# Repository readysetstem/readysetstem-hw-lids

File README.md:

readysetstem-hw-lids
===========================

Ready Set STEM(TM) Lids hardware schematics and related documents

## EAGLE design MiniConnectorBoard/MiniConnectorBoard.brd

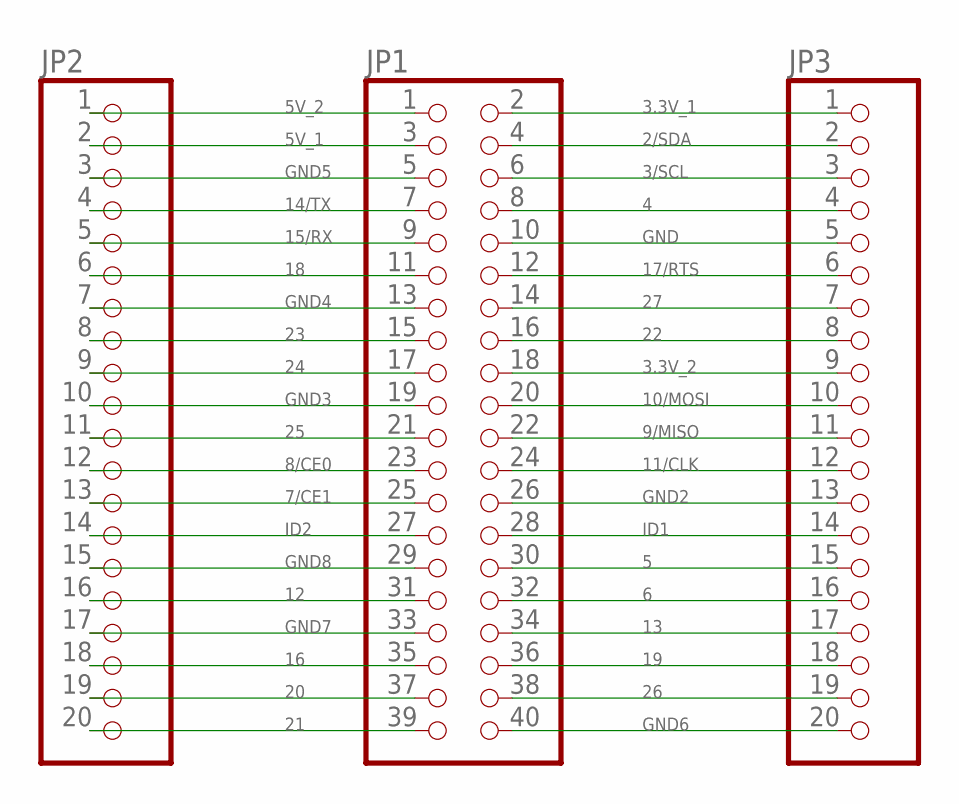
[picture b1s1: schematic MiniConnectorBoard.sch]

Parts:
JP1: NONE; 2X20
JP2, JP3: NONE; 1X20

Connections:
2/SDA: JP1.4, JP3.2
3.3V_1: JP1.2, JP3.1
3.3V_2: JP1.18, JP3.9
3/SCL: JP1.6, JP3.3
4: JP1.8, JP3.4
5: JP1.30, JP3.15
5V_1: JP1.3, JP2.2
5V_2: JP1.1, JP2.1
6: JP1.32, JP3.16
7/CE1: JP1.25, JP2.13
8/CE0: JP1.23, JP2.12
9/MISO: JP1.22, JP3.11
10/MOSI: JP1.20, JP3.10
11/CLK: JP1.24, JP3.12
12: JP1.31, JP2.16
13: JP1.34, JP3.17
14/TX: JP1.7, JP2.4
15/RX: JP1.9, JP2.5
16: JP1.35, JP2.18
17/RTS: JP1.12, JP3.6
18: JP1.11, JP2.6
19: JP1.36, JP3.18
20: JP1.37, JP2.19
21: JP1.39, JP2.20
22: JP1.16, JP3.8
23: JP1.15, JP2.8
24: JP1.17, JP2.9
25: JP1.21, JP2.11
26: JP1.38, JP3.19
27: JP1.14, JP3.7
GND: JP1.10, JP3.5
GND2: JP1.26, JP3.13
GND3: JP1.19, JP2.10
GND4: JP1.13, JP2.7
GND5: JP1.5, JP2.3
GND6: JP1.40, JP3.20
GND7: JP1.33, JP2.17
GND8: JP1.29, JP2.15
ID1: JP1.28, JP3.14
ID2: JP1.27, JP2.14

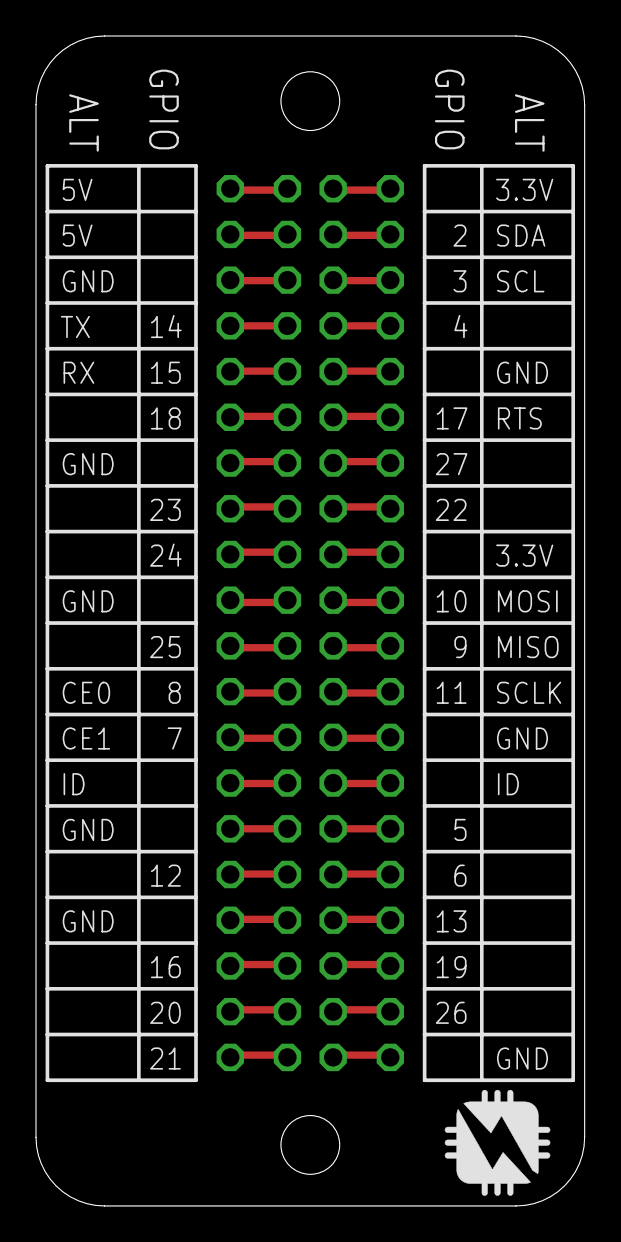
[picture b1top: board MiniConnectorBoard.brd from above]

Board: 2 copper layers, 30.5 x 65.0 mm, 3 parts (0 on the bottom side), 40 nets.

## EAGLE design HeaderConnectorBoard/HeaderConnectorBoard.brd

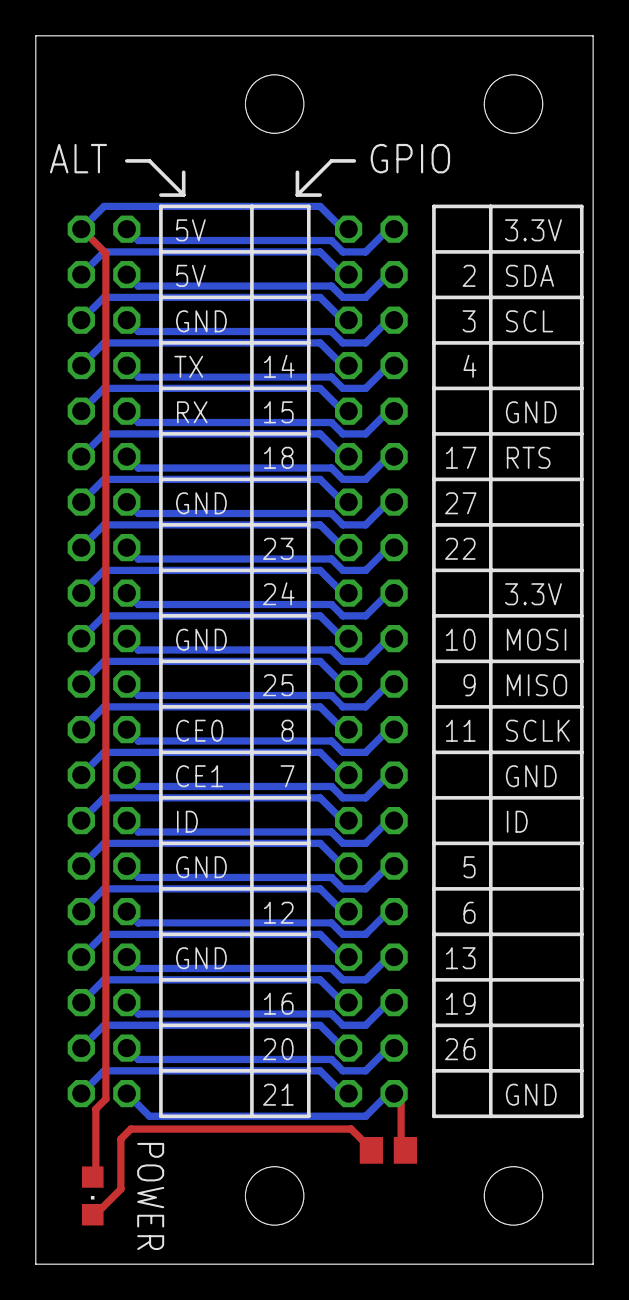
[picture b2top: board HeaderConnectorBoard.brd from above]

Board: 2 copper layers, 31.1 x 68.6 mm, 4 parts (0 on the bottom side), 41 nets.

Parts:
JP1, JP2: NONE; 2X20
LED1: 475-1410-2-ND; CHIPLED_0805
R1: 200; R0805

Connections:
2/SDA: JP1.4, JP2.4
3.3V_1: JP1.2, JP2.2
3.3V_2: JP1.18, JP2.18
3/SCL: JP1.6, JP2.6
4: JP1.8, JP2.8
5: JP1.30, JP2.30
5V_1: JP1.3, JP2.3
5V_2: JP1.1, JP2.1, LED1.A
6: JP1.32, JP2.32
7/CE1: JP1.25, JP2.25
8/CE0: JP1.23, JP2.23
9/MISO: JP1.22, JP2.22
10/MOSI: JP1.20, JP2.20
11/CLK: JP1.24, JP2.24
12: JP1.31, JP2.31
13: JP1.34, JP2.34
14/TX: JP1.7, JP2.7
15/RX: JP1.9, JP2.9
16: JP1.35, JP2.35
17/RTS: JP1.12, JP2.12
18: JP1.11, JP2.11
19: JP1.36, JP2.36
20: JP1.37, JP2.37
21: JP1.39, JP2.39
22: JP1.16, JP2.16
23: JP1.15, JP2.15
24: JP1.17, JP2.17
25: JP1.21, JP2.21
26: JP1.38, JP2.38
27: JP1.14, JP2.14
GND: JP1.10, JP2.10
GND2: JP1.26, JP2.26
GND3: JP1.19, JP2.19
GND4: JP1.13, JP2.13
GND5: JP1.5, JP2.5
GND6: JP1.40, JP2.40, R1.1
GND7: JP1.33, JP2.33
GND8: JP1.29, JP2.29
ID1: JP1.28, JP2.28
ID2: JP1.27, JP2.27
unnamed: LED1.C, R1.2

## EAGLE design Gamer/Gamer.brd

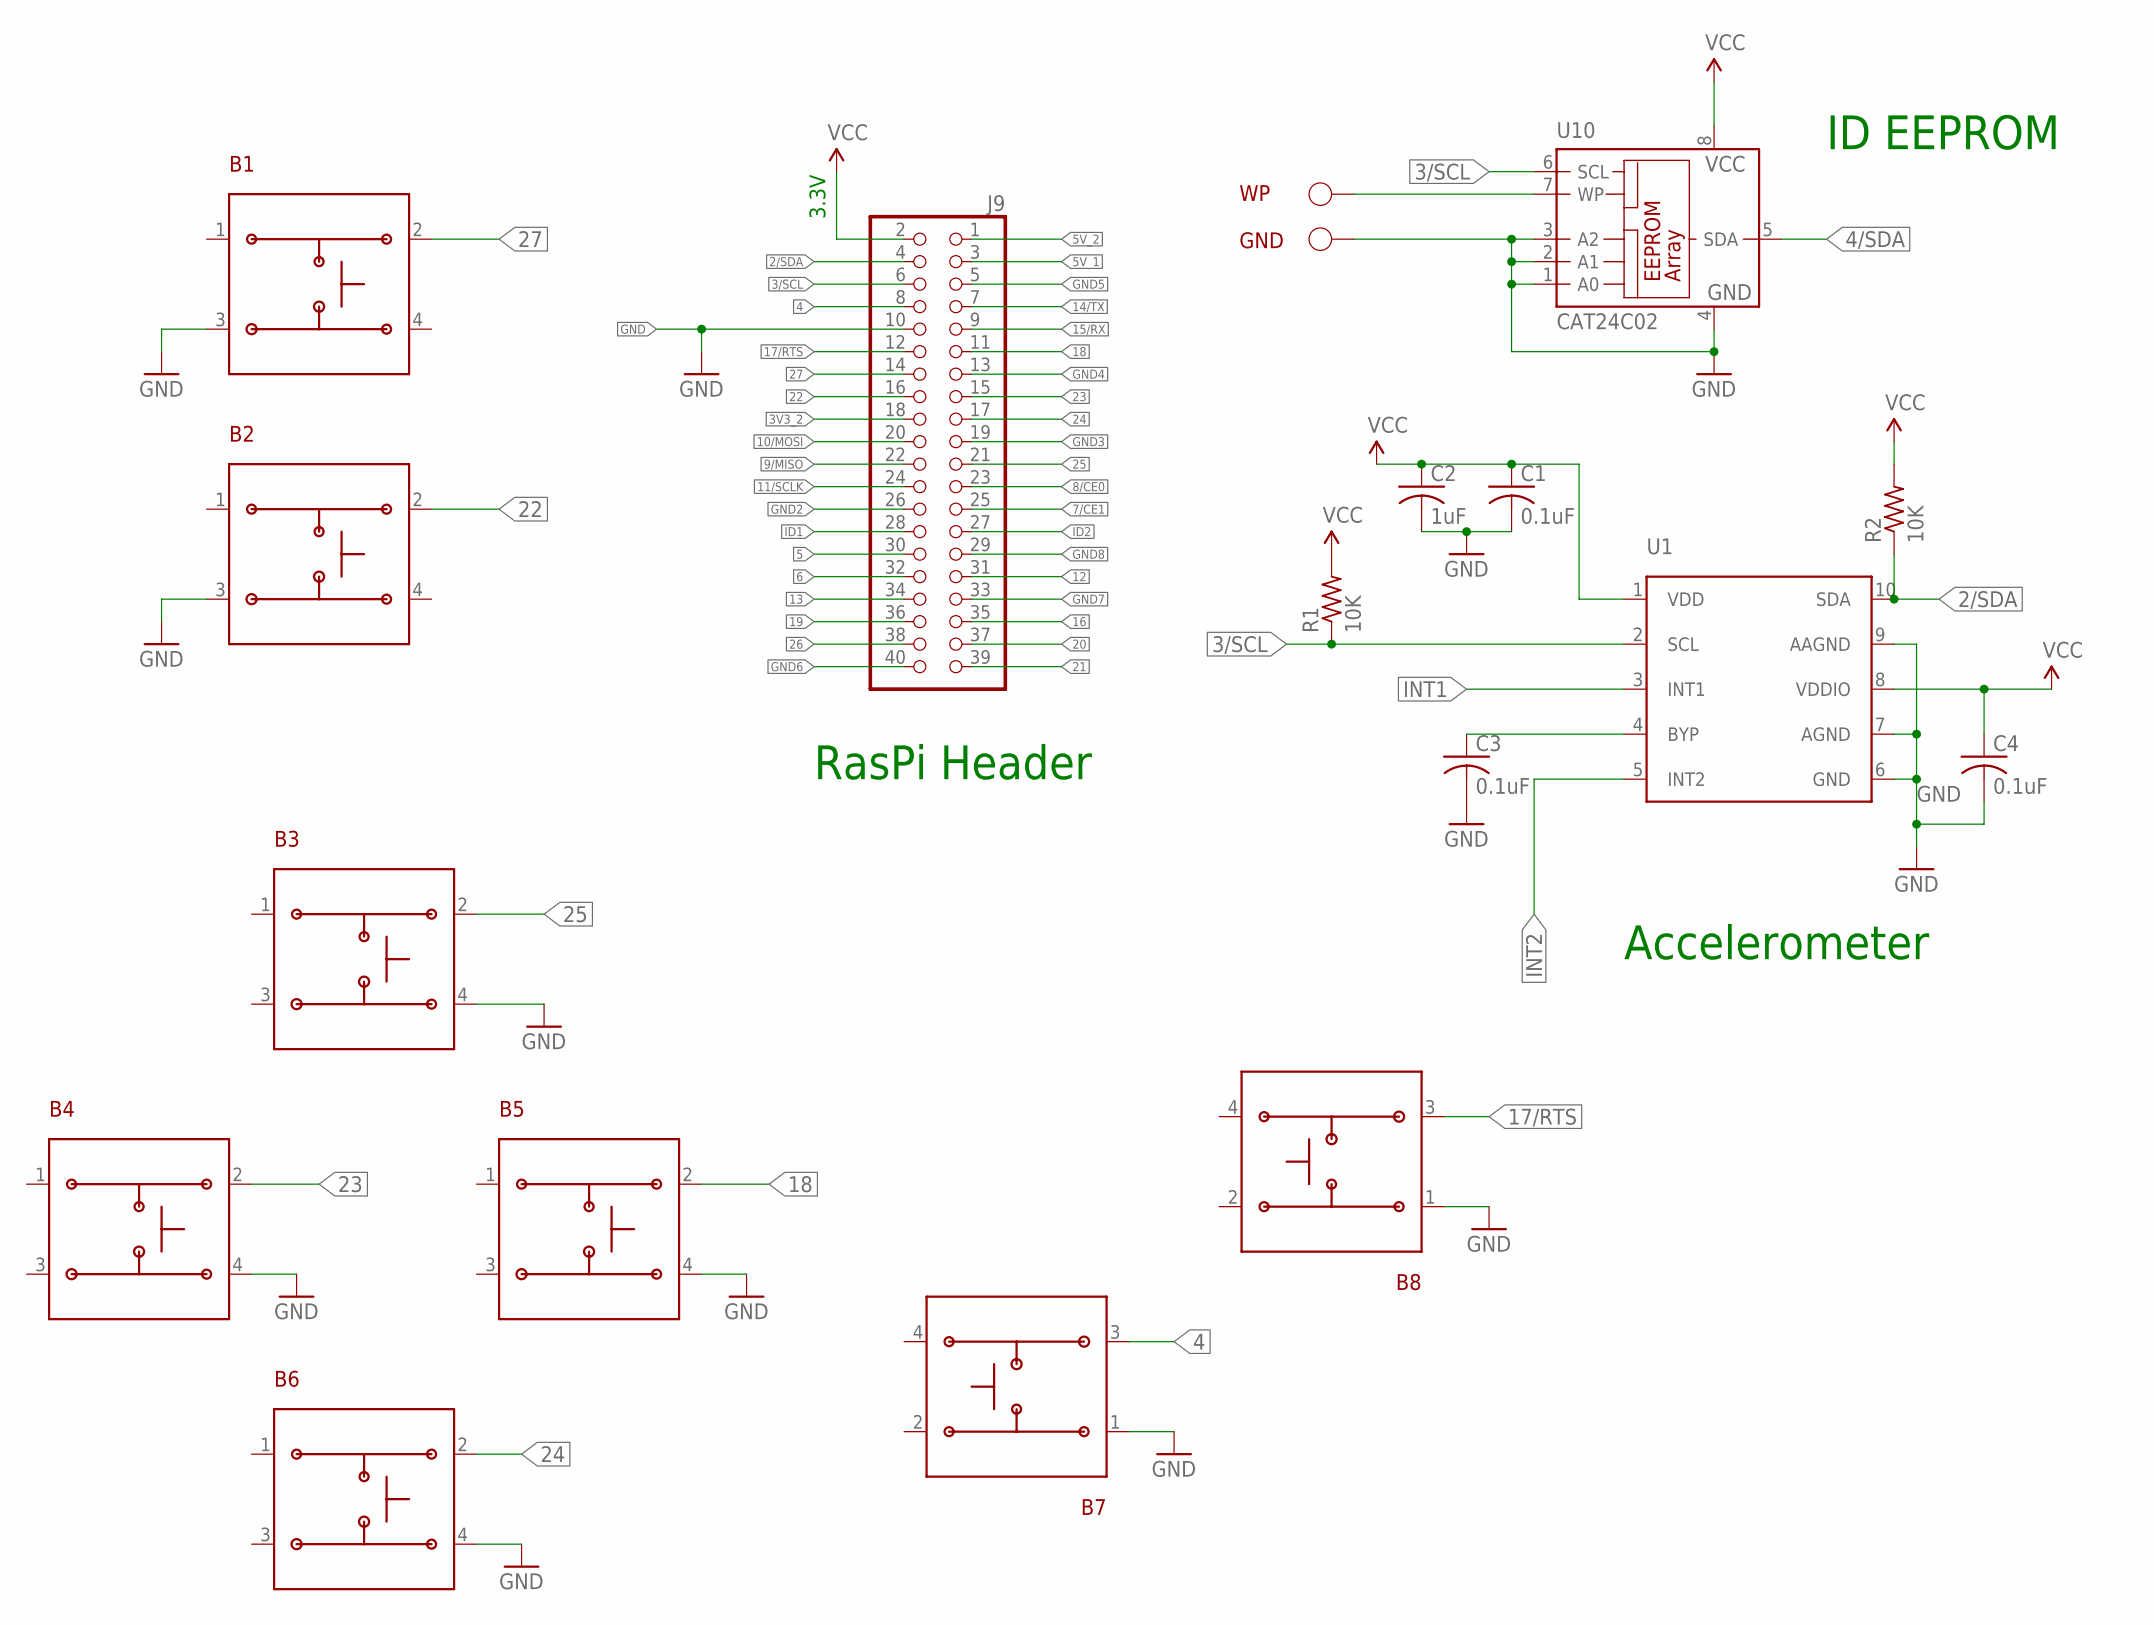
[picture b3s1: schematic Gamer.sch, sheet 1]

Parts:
B1, B2: 6X6MM_BUTTON
B3, B4, B5, B6, B7, B8: 12X12MM_BUTTON
C1, C3, C4: 0.1uF; C0603
C2: 1uF; C0603
GND: TESTPAD
J9: PINHD-2X20; 2X20
R1, R2: 10K; R0603
U1: MMA8653FCR1
U10: CAT24C02; TSSOP8
WP: TESTPAD

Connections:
2/SDA: J9.4, R2.1, U1.10 (SDA)
3/SCL: J9.6, R1.1, U1.2 (SCL), U10.6 (SCL)
3V3_2: J9.18
4: B7.3, J9.8
4/SDA: U10.5 (SDA)
5: J9.30
5V_1: J9.3
5V_2: J9.1
6: J9.32
7/CE1: J9.25
8/CE0: J9.23; also elsewhere on the board
9/MISO: J9.22; also elsewhere on the board
10/MOSI: J9.20; also elsewhere on the board
11/SCLK: J9.24; also elsewhere on the board
12: J9.31
13: J9.34
14/TX: J9.7
15/RX: J9.9
16: J9.35
17/RTS: B8.3, J9.12
18: B5.2, J9.11
19: J9.36
20: J9.37
21: J9.39
22: B2.2, J9.16
23: B4.2, J9.15
24: B6.2, J9.17
25: B3.2, J9.21
26: J9.38
27: B1.2, J9.14
GND: B1.3, B2.3, B3.4, B4.4, B5.4, B6.4, B7.1, B8.1, C1.2, C2.2, C3.2, C4.2, GND.1, J9.10, U1.6 (GND), U1.7 (AGND), U1.9 (AAGND), U10.1 (A0), U10.2 (A1), U10.3 (A2), U10.4 (GND); also elsewhere on the board
GND2: J9.26
GND3: J9.19
GND4: J9.13
GND5: J9.5
GND6: J9.40
GND7: J9.33
GND8: J9.29
ID1: J9.28
ID2: J9.27
INT1: U1.3 (INT1)
INT2: U1.5 (INT2)
unnamed: U10.7 (WP), WP.1
unnamed: C3.1, U1.4 (BYP)
VCC: C1.1, C2.1, C4.1, J9.2, R1.2, R2.2, U1.1 (VDD), U1.8 (VDDIO), U10.8 (VCC); also elsewhere on the board

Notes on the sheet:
RasPi Header
Accelerometer
3.3V
ID EEPROM

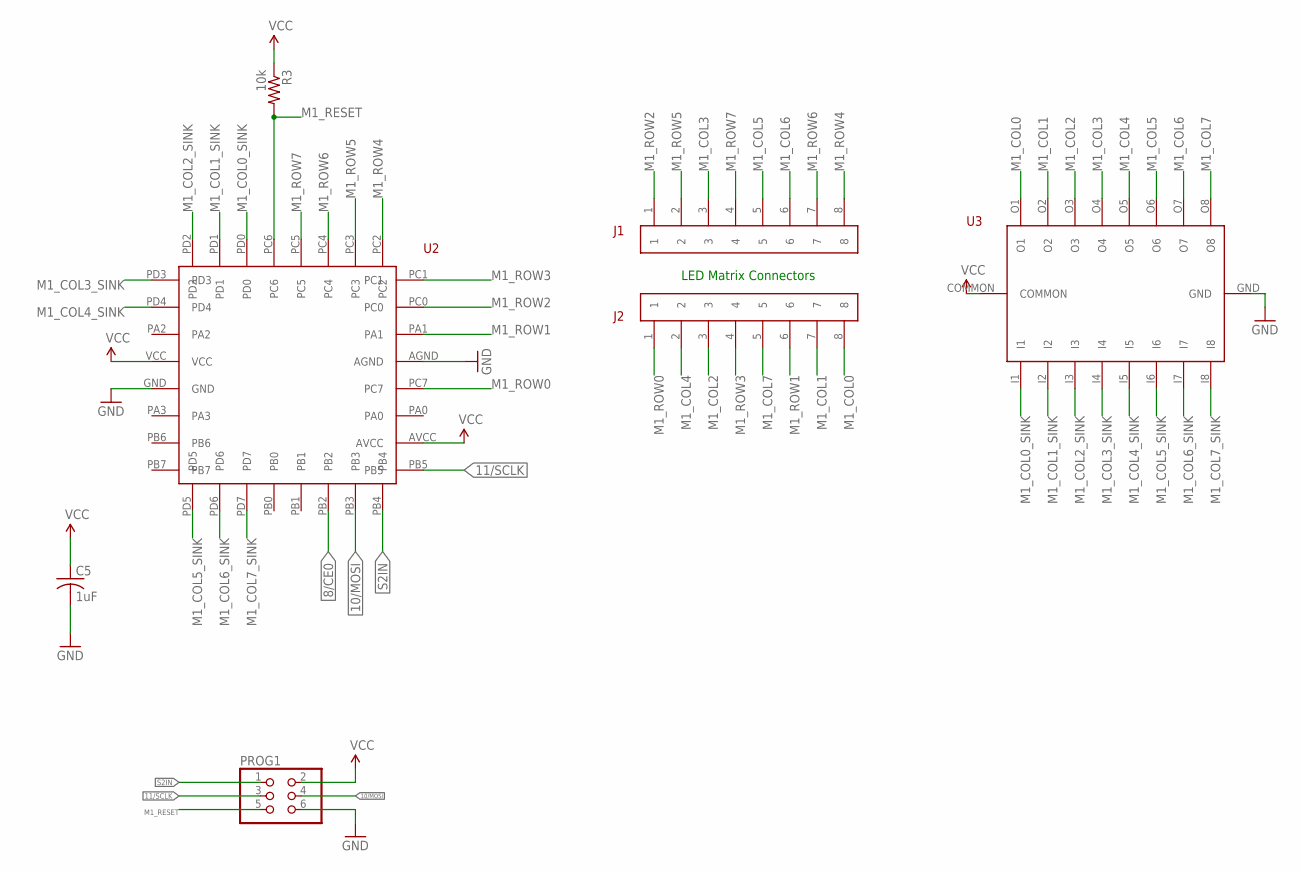
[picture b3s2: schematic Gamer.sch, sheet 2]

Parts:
C5: 1uF; C0603
J1, J2: HEADER-1X8
PROG1: NONE; 2X03
R3: 10k; R0603
U2: ATTINY48
U3: ULN2803AFWG

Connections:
8/CE0: U2.PB2; also elsewhere on the board
10/MOSI: PROG1.4, U2.PB3; also elsewhere on the board
11/SCLK: PROG1.3, U2.PB5; also elsewhere on the board
GND: C5.2, PROG1.6, U2.AGND, U2.GND, U3.GND; also elsewhere on the board
M1_COL0: J2.8, U3.O1
M1_COL0_SINK: U2.PD0, U3.I1
M1_COL1: J2.7, U3.O2
M1_COL1_SINK: U2.PD1, U3.I2
M1_COL2: J2.3, U3.O3
M1_COL2_SINK: U2.PD2, U3.I3
M1_COL3: J1.3, U3.O4
M1_COL3_SINK: U2.PD3, U3.I4
M1_COL4: J2.2, U3.O5
M1_COL4_SINK: U2.PD4, U3.I5
M1_COL5: J1.5, U3.O6
M1_COL5_SINK: U2.PD5, U3.I6
M1_COL6: J1.6, U3.O7
M1_COL6_SINK: U2.PD6, U3.I7
M1_COL7: J2.5, U3.O8
M1_COL7_SINK: U2.PD7, U3.I8
M1_RESET: PROG1.5, R3.2, U2.PC6
M1_ROW0: J2.1, U2.PC7
M1_ROW1: J2.6, U2.PA1
M1_ROW2: J1.1, U2.PC0
M1_ROW3: J2.4, U2.PC1
M1_ROW4: J1.8, U2.PC2
M1_ROW5: J1.2, U2.PC3
M1_ROW6: J1.7, U2.PC4
M1_ROW7: J1.4, U2.PC5
S2IN: PROG1.1, U2.PB4; also elsewhere on the board
VCC: C5.1, PROG1.2, R3.1, U2.AVCC, U2.VCC, U3.COMMON; also elsewhere on the board

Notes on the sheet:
LED Matrix Connectors

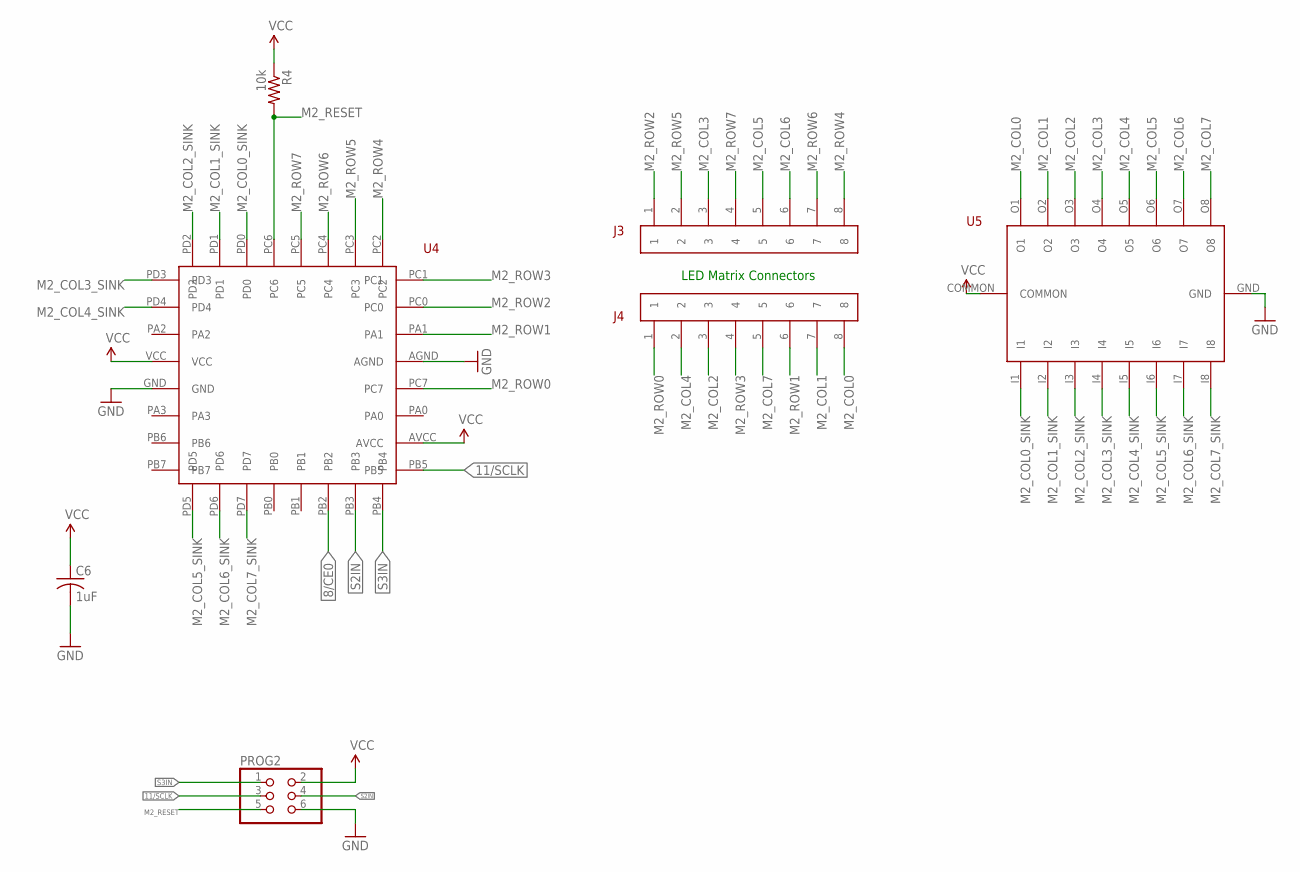
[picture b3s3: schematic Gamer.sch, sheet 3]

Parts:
C6: 1uF; C0603
J3, J4: HEADER-1X8
PROG2: NONE; 2X03
R4: 10k; R0603
U4: ATTINY48
U5: ULN2803AFWG

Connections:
8/CE0: U4.PB2; also elsewhere on the board
11/SCLK: PROG2.3, U4.PB5; also elsewhere on the board
GND: C6.2, PROG2.6, U4.AGND, U4.GND, U5.GND; also elsewhere on the board
M2_COL0: J4.8, U5.O1
M2_COL0_SINK: U4.PD0, U5.I1
M2_COL1: J4.7, U5.O2
M2_COL1_SINK: U4.PD1, U5.I2
M2_COL2: J4.3, U5.O3
M2_COL2_SINK: U4.PD2, U5.I3
M2_COL3: J3.3, U5.O4
M2_COL3_SINK: U4.PD3, U5.I4
M2_COL4: J4.2, U5.O5
M2_COL4_SINK: U4.PD4, U5.I5
M2_COL5: J3.5, U5.O6
M2_COL5_SINK: U4.PD5, U5.I6
M2_COL6: J3.6, U5.O7
M2_COL6_SINK: U4.PD6, U5.I7
M2_COL7: J4.5, U5.O8
M2_COL7_SINK: U4.PD7, U5.I8
M2_RESET: PROG2.5, R4.2, U4.PC6
M2_ROW0: J4.1, U4.PC7
M2_ROW1: J4.6, U4.PA1
M2_ROW2: J3.1, U4.PC0
M2_ROW3: J4.4, U4.PC1
M2_ROW4: J3.8, U4.PC2
M2_ROW5: J3.2, U4.PC3
M2_ROW6: J3.7, U4.PC4
M2_ROW7: J3.4, U4.PC5
S2IN: PROG2.4, U4.PB3; also elsewhere on the board
S3IN: PROG2.1, U4.PB4; also elsewhere on the board
VCC: C6.1, PROG2.2, R4.1, U4.AVCC, U4.VCC, U5.COMMON; also elsewhere on the board

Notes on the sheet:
LED Matrix Connectors

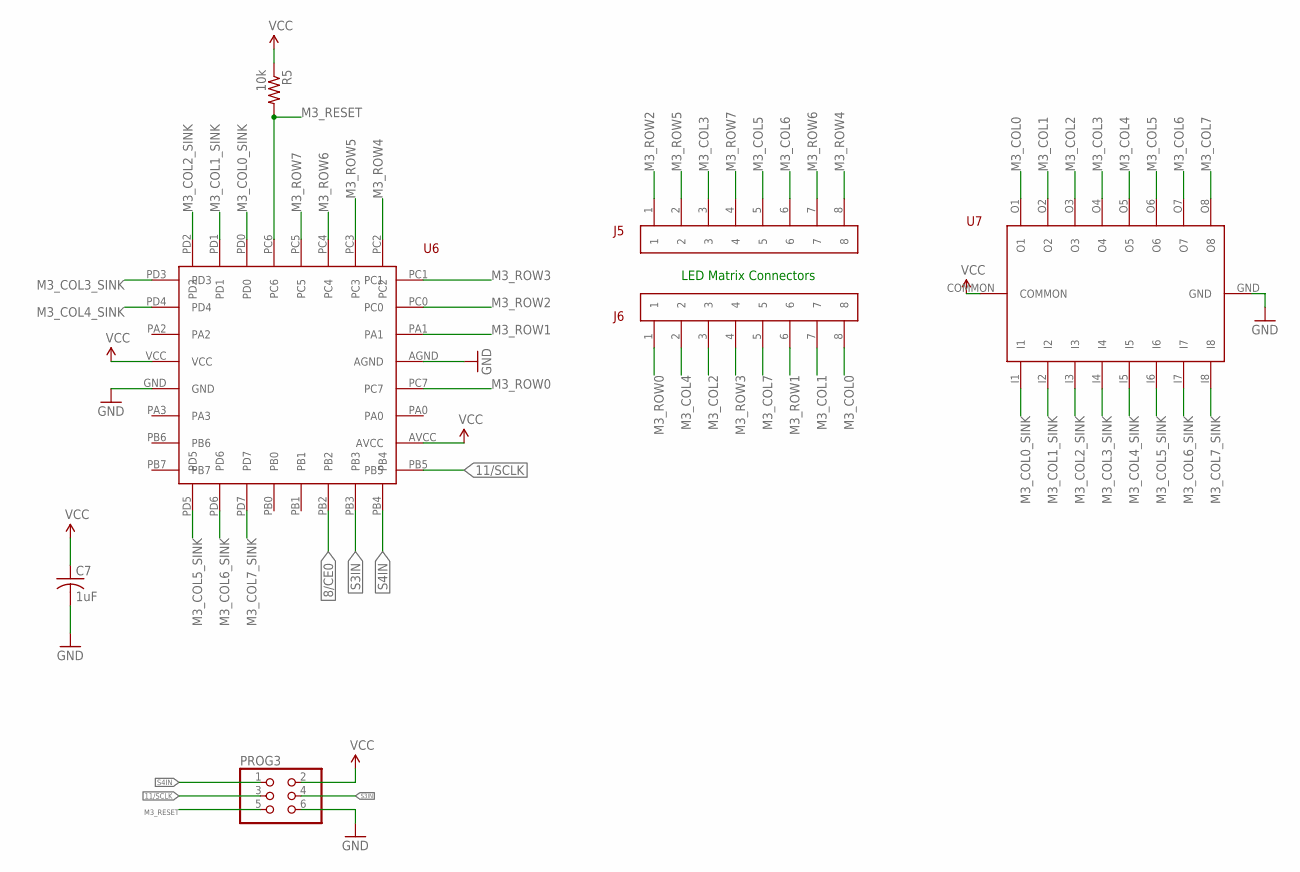
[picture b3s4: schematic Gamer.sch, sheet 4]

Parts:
C7: 1uF; C0603
J5, J6: HEADER-1X8
PROG3: NONE; 2X03
R5: 10k; R0603
U6: ATTINY48
U7: ULN2803AFWG

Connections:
8/CE0: U6.PB2; also elsewhere on the board
11/SCLK: PROG3.3, U6.PB5; also elsewhere on the board
GND: C7.2, PROG3.6, U6.AGND, U6.GND, U7.GND; also elsewhere on the board
M3_COL0: J6.8, U7.O1
M3_COL0_SINK: U6.PD0, U7.I1
M3_COL1: J6.7, U7.O2
M3_COL1_SINK: U6.PD1, U7.I2
M3_COL2: J6.3, U7.O3
M3_COL2_SINK: U6.PD2, U7.I3
M3_COL3: J5.3, U7.O4
M3_COL3_SINK: U6.PD3, U7.I4
M3_COL4: J6.2, U7.O5
M3_COL4_SINK: U6.PD4, U7.I5
M3_COL5: J5.5, U7.O6
M3_COL5_SINK: U6.PD5, U7.I6
M3_COL6: J5.6, U7.O7
M3_COL6_SINK: U6.PD6, U7.I7
M3_COL7: J6.5, U7.O8
M3_COL7_SINK: U6.PD7, U7.I8
M3_RESET: PROG3.5, R5.2, U6.PC6
M3_ROW0: J6.1, U6.PC7
M3_ROW1: J6.6, U6.PA1
M3_ROW2: J5.1, U6.PC0
M3_ROW3: J6.4, U6.PC1
M3_ROW4: J5.8, U6.PC2
M3_ROW5: J5.2, U6.PC3
M3_ROW6: J5.7, U6.PC4
M3_ROW7: J5.4, U6.PC5
S3IN: PROG3.4, U6.PB3; also elsewhere on the board
S4IN: PROG3.1, U6.PB4; also elsewhere on the board
VCC: C7.1, PROG3.2, R5.1, U6.AVCC, U6.VCC, U7.COMMON; also elsewhere on the board

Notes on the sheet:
LED Matrix Connectors

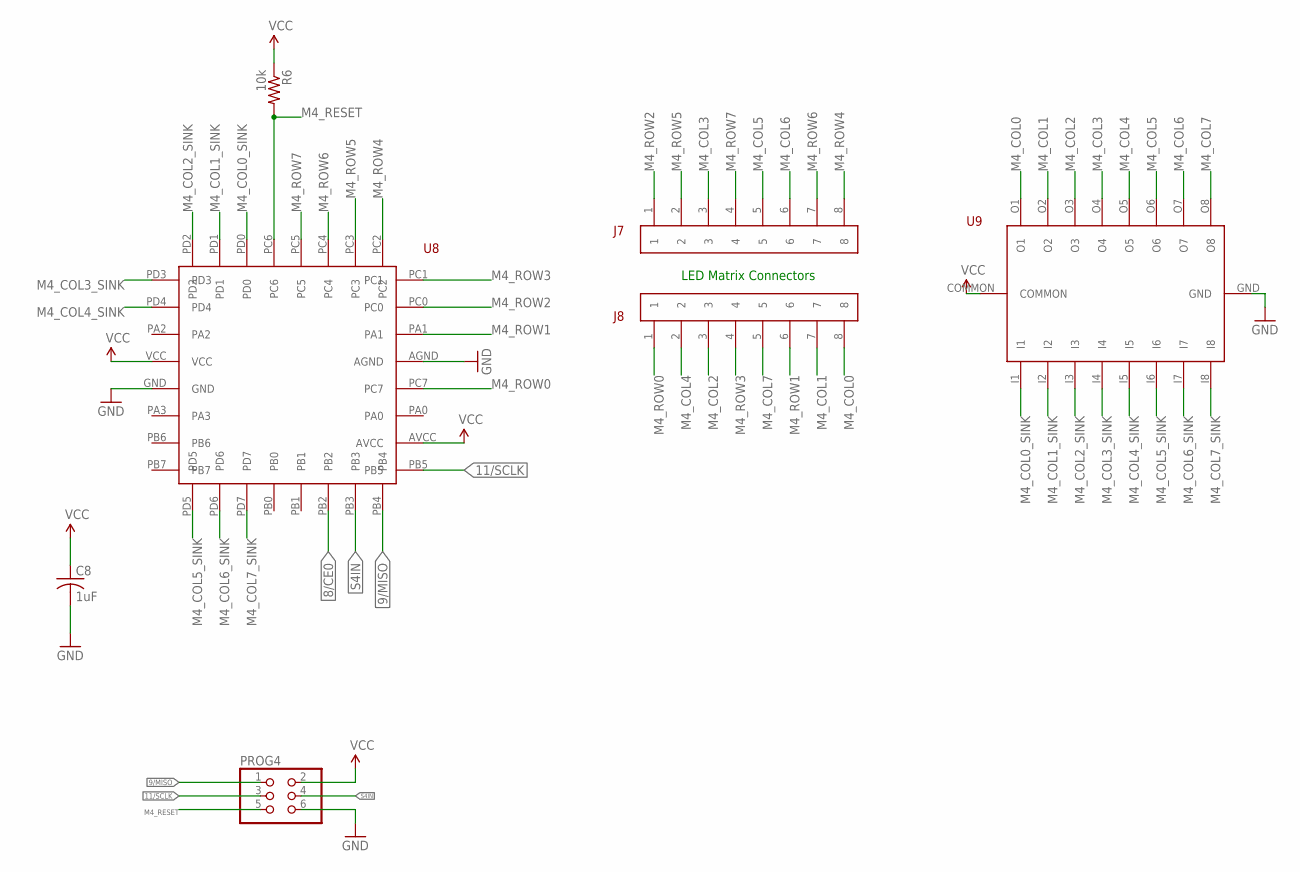
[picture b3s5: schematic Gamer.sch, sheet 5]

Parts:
C8: 1uF; C0603
J7, J8: HEADER-1X8
PROG4: NONE; 2X03
R6: 10k; R0603
U8: ATTINY48
U9: ULN2803AFWG

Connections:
8/CE0: U8.PB2; also elsewhere on the board
9/MISO: PROG4.1, U8.PB4; also elsewhere on the board
11/SCLK: PROG4.3, U8.PB5; also elsewhere on the board
GND: C8.2, PROG4.6, U8.AGND, U8.GND, U9.GND; also elsewhere on the board
M4_COL0: J8.8, U9.O1
M4_COL0_SINK: U8.PD0, U9.I1
M4_COL1: J8.7, U9.O2
M4_COL1_SINK: U8.PD1, U9.I2
M4_COL2: J8.3, U9.O3
M4_COL2_SINK: U8.PD2, U9.I3
M4_COL3: J7.3, U9.O4
M4_COL3_SINK: U8.PD3, U9.I4
M4_COL4: J8.2, U9.O5
M4_COL4_SINK: U8.PD4, U9.I5
M4_COL5: J7.5, U9.O6
M4_COL5_SINK: U8.PD5, U9.I6
M4_COL6: J7.6, U9.O7
M4_COL6_SINK: U8.PD6, U9.I7
M4_COL7: J8.5, U9.O8
M4_COL7_SINK: U8.PD7, U9.I8
M4_RESET: PROG4.5, R6.2, U8.PC6
M4_ROW0: J8.1, U8.PC7
M4_ROW1: J8.6, U8.PA1
M4_ROW2: J7.1, U8.PC0
M4_ROW3: J8.4, U8.PC1
M4_ROW4: J7.8, U8.PC2
M4_ROW5: J7.2, U8.PC3
M4_ROW6: J7.7, U8.PC4
M4_ROW7: J7.4, U8.PC5
S4IN: PROG4.4, U8.PB3; also elsewhere on the board
VCC: C8.1, PROG4.2, R6.1, U8.AVCC, U8.VCC, U9.COMMON; also elsewhere on the board

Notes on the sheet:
LED Matrix Connectors

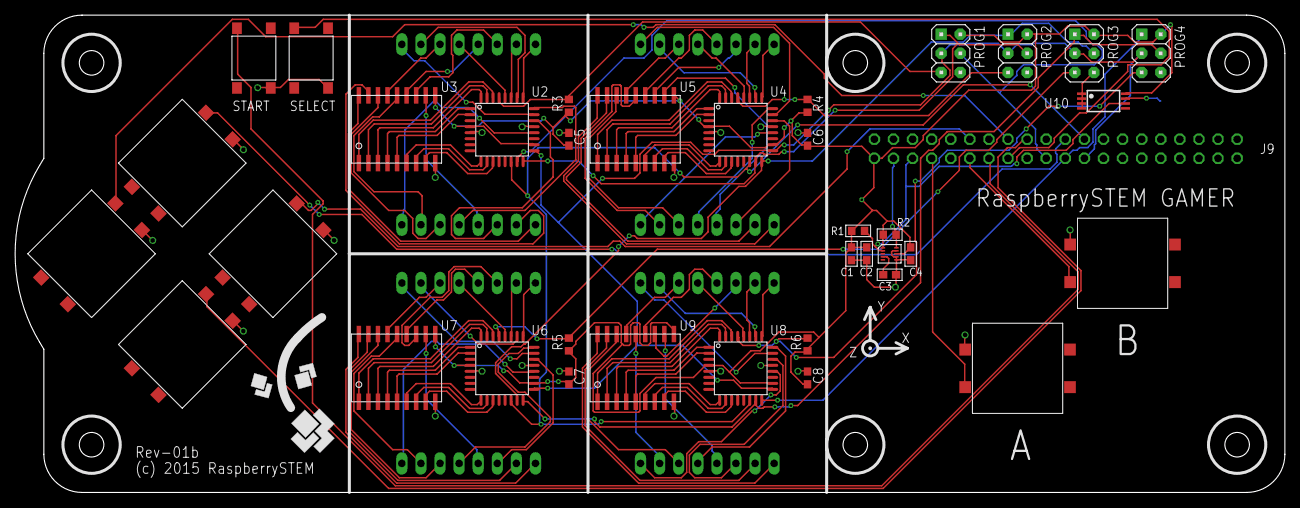
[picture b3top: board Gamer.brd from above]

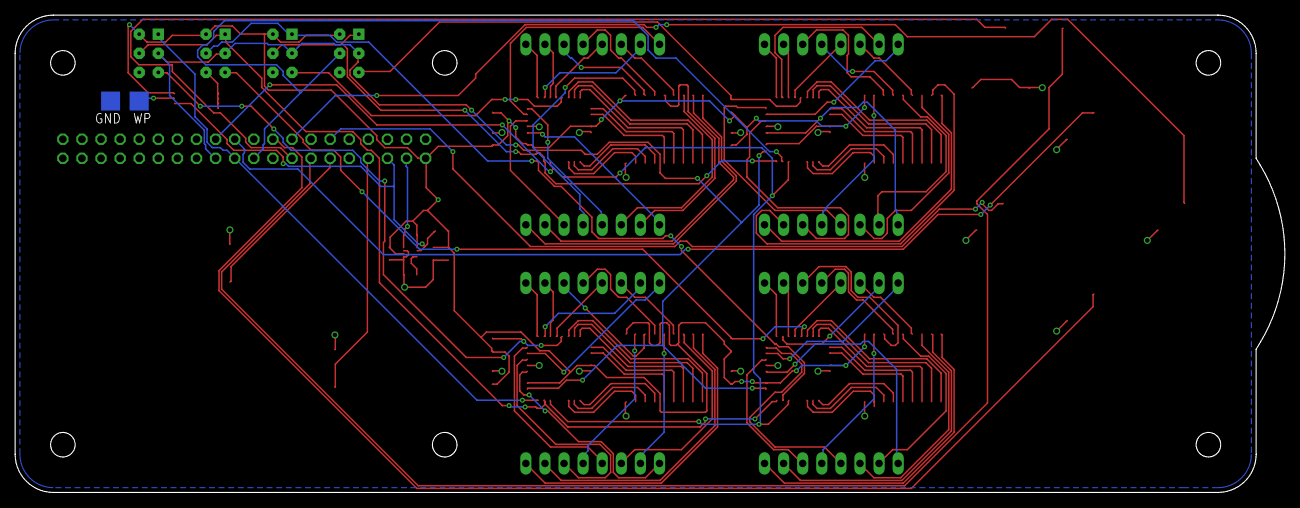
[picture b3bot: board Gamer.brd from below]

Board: 2 copper layers, 168.9 x 63.5 mm, 47 parts (3 on the bottom side), 121 nets.

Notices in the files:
Gamer/Gamer.brd:
(c) 2015 RaspberrySTEM
HeaderConnectorBoard/HeaderConnectorBoard.brd:
(c) 2016 Ready Set STEM
parts and their libraries:
SparkFun-Aesthetics: Licensing: Creative Commons ShareAlike 4.0 International - https://creativecommons.org/licenses/by-sa/4.0
